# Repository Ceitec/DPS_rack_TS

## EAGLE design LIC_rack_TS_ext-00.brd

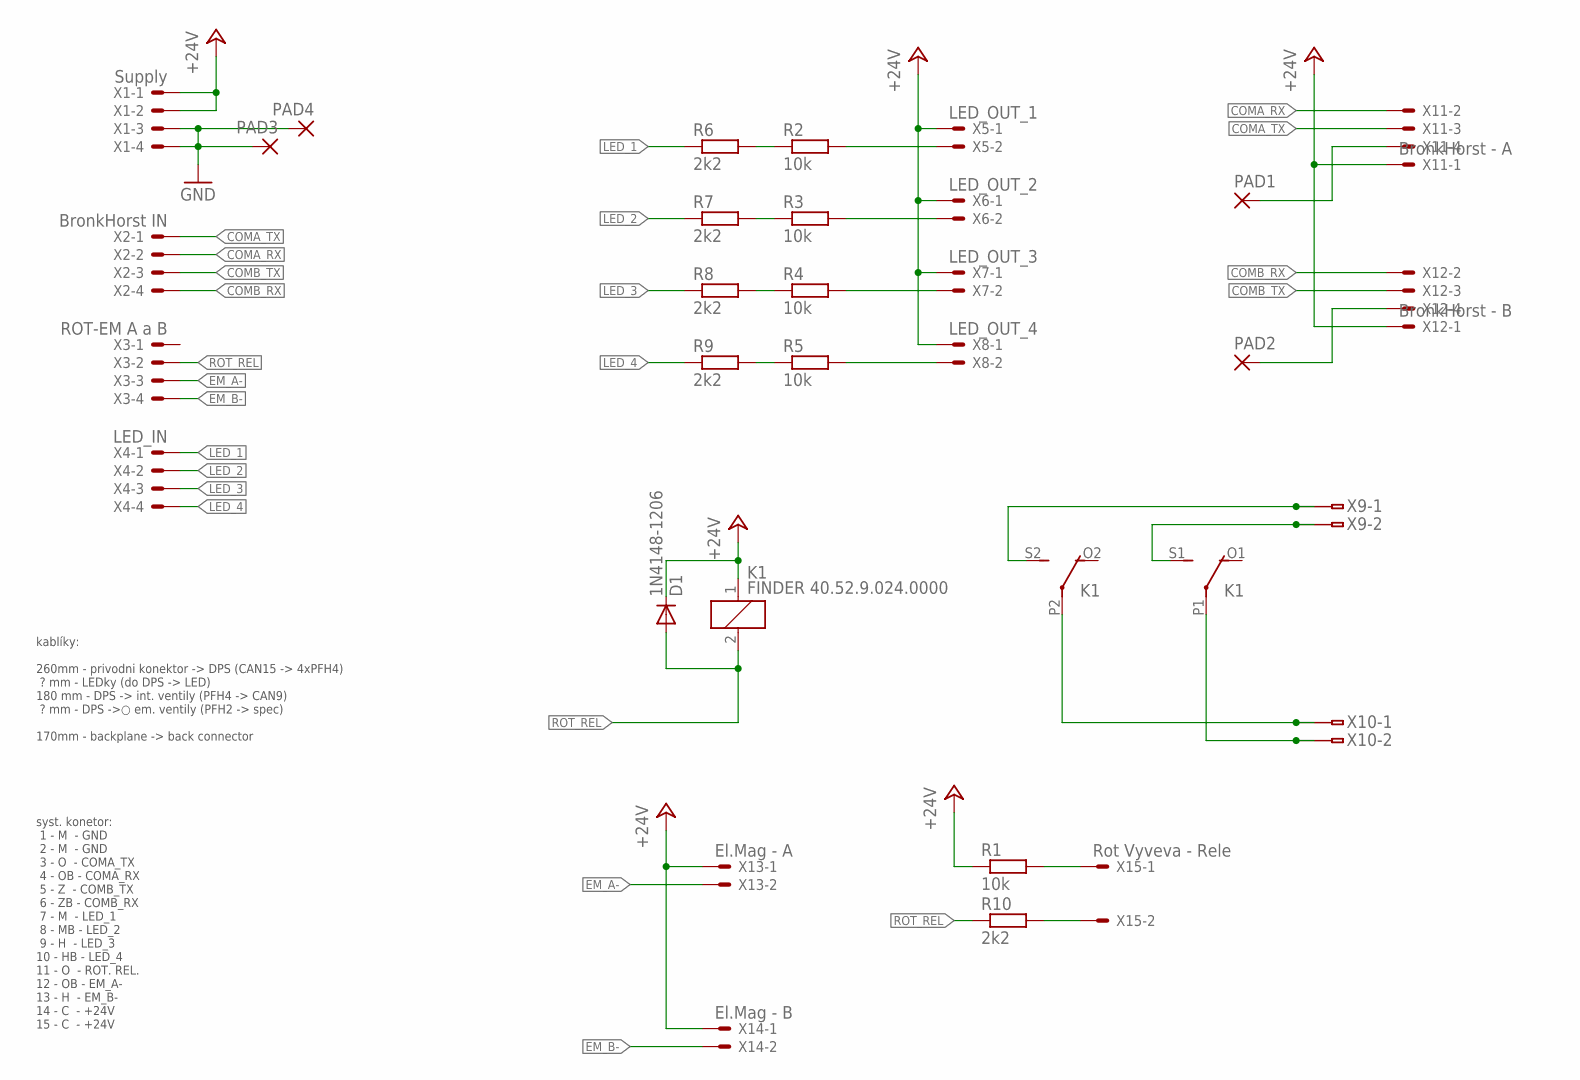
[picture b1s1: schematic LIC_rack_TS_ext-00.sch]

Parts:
D1: 1N4148-1206; R1206
K1: FINDER 40.52.9.024.0000; F4052
PAD1, PAD2, PAD3, PAD4: SMD-2X3; SMD2-3
R1, R2, R3, R4, R5: 10k; R1206
R6, R7, R8, R9, R10: 2k2; R1206
X1: Supply; 22-23-2041
X2: BronkHorst IN; 22-23-2041
X3: ROT-EM A a B; 22-23-2041
X4: LED_IN; 22-23-2041
X5: LED_OUT_1; 22-23-2021
X6: LED_OUT_2; 22-23-2021
X7: LED_OUT_3; 22-23-2021
X8: LED_OUT_4; 22-23-2021
X9: High Voltage Supply - L; WAGO236-401_2
X10: High Voltage Supply - N; WAGO236-401_2
X11: BronkHorst - A; 22-23-2041
X12: BronkHorst - B; 22-23-2041
X13: El.Mag - A; 22-23-2021
X14: El.Mag - B; 22-23-2021
X15: Rot Vyveva - Rele; 22-23-2021

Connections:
+24V: D1.K (C), K1.1, R1.1, X1.1, X1.2, X5.1, X6.1, X7.1, X8.1, X11.1, X12.1, X13.1, X14.1
COMA_RX: X2.2, X11.2
COMA_TX: X2.1, X11.3
COMB_RX: X2.4, X12.2
COMB_TX: X2.3, X12.3
EM_A-: X3.3, X13.2
EM_B-: X3.4, X14.2
GND: PAD3.1, PAD4.1, X1.3, X1.4
LED_1: R6.1, X4.1
LED_2: R7.1, X4.2
LED_3: R8.1, X4.3
LED_4: R9.1, X4.4
unnamed: K1.S1 (S), X9.2A (1), X9.2B (2)
unnamed: K1.S2 (S), X9.1A (1), X9.1B (2)
unnamed: K1.P1, X10.2A (1), X10.2B (2)
unnamed: K1.P2, X10.1A (1), X10.1B (2)
unnamed: R2.2, X5.2
unnamed: R3.2, X6.2
unnamed: R4.2, X7.2
unnamed: R5.2, X8.2
unnamed: R2.1, R6.2
unnamed: R3.1, R7.2
unnamed: R4.1, R8.2
unnamed: R5.1, R9.2
unnamed: PAD1.1, X11.4
unnamed: PAD2.1, X12.4
unnamed: R10.2, X15.2
unnamed: R1.2, X15.1
ROT_REL: D1.A, K1.2, R10.1, X3.2

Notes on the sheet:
kablíky: 260mm - privodni konektor -> DPS (CAN15 -> 4xPFH4) ? mm - LEDky (do DPS -> LED) 180 mm - DPS -> int. ventily (PFH4 -> CAN9) ? mm - DPS ->○ em. ventily (PFH2 -> spec) 170mm - backplane -> back connector
syst. konetor: 1 - M - GND 2 - M - GND 3 - O - COMA_TX 4 - OB - COMA_RX 5 - Z - COMB_TX 6 - ZB - COMB_RX 7 - M - LED_1 8 - MB - LED_2 9 - H - LED_3 10 - HB - LED_4 11 - O - ROT. REL. 12 - OB - EM_A- 13 - H - EM_B- 14 - C - +24V 15 - C - +24V

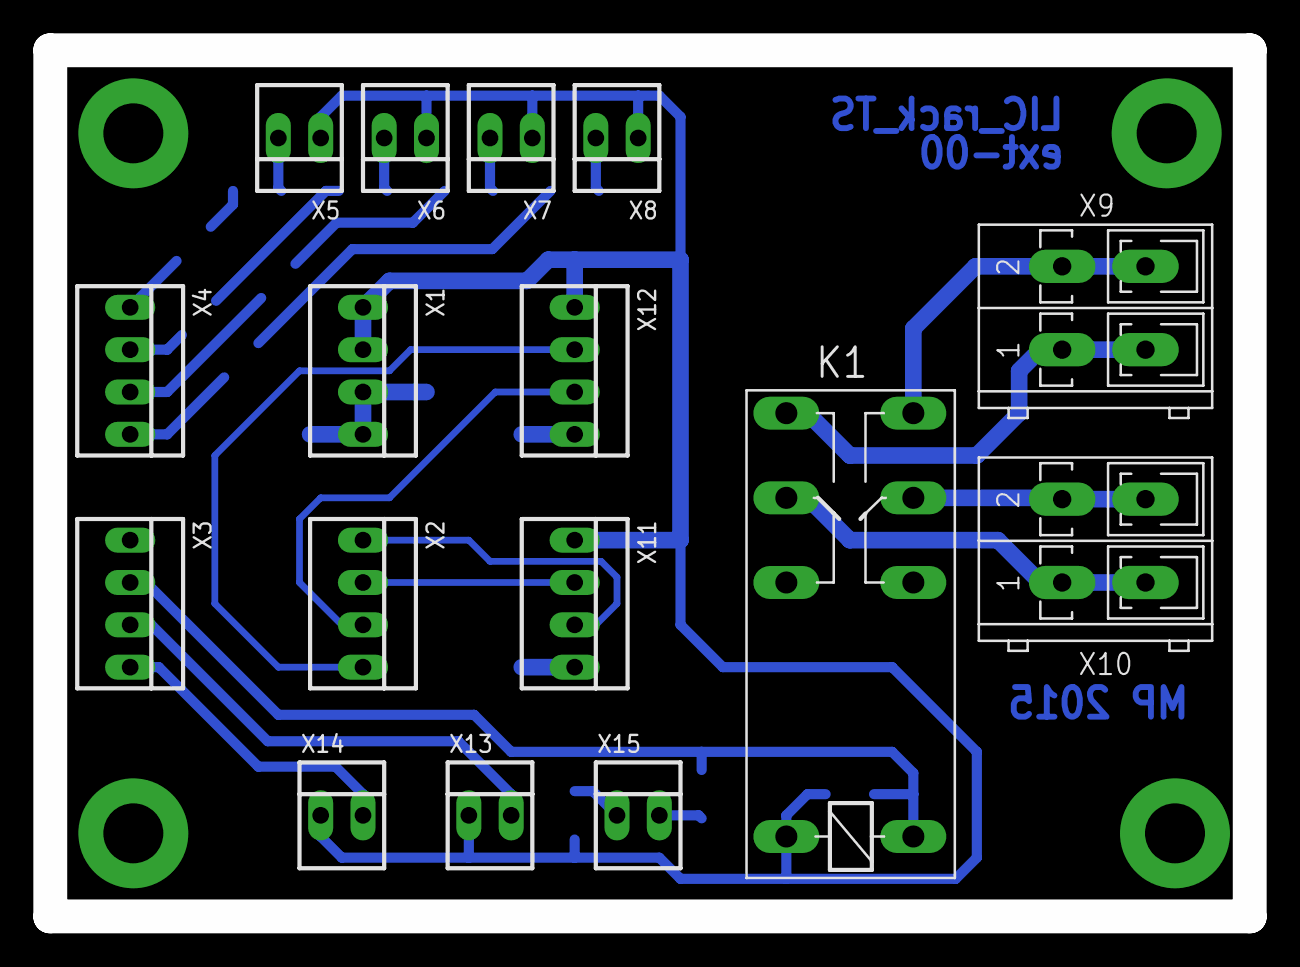
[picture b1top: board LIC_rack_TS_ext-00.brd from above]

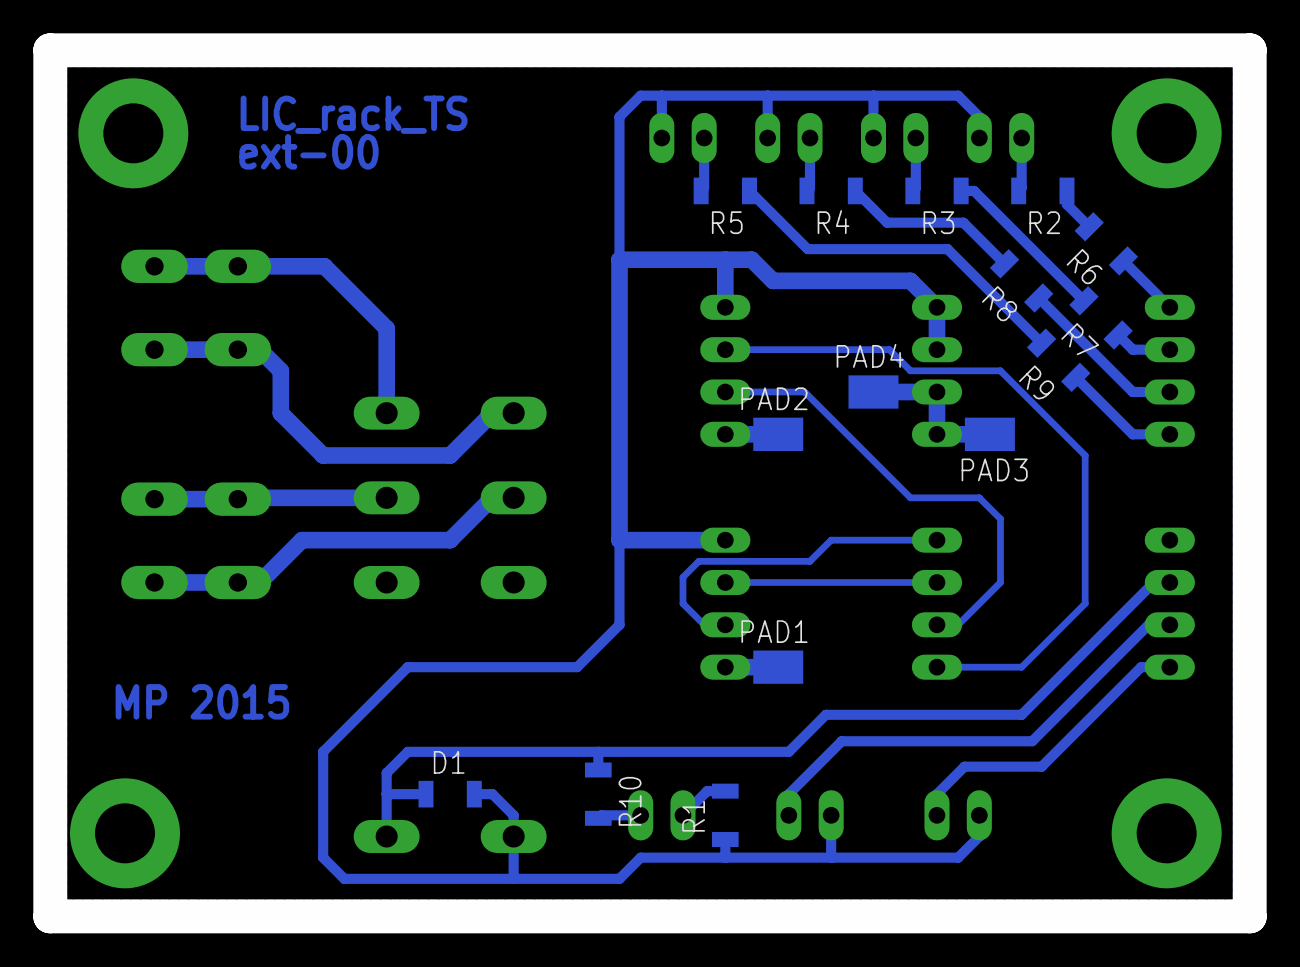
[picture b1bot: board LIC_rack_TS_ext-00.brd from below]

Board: 2 copper layers, 72.0 x 52.0 mm, 32 parts (15 on the bottom side), 29 nets.

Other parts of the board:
U$2: A4L-LOC

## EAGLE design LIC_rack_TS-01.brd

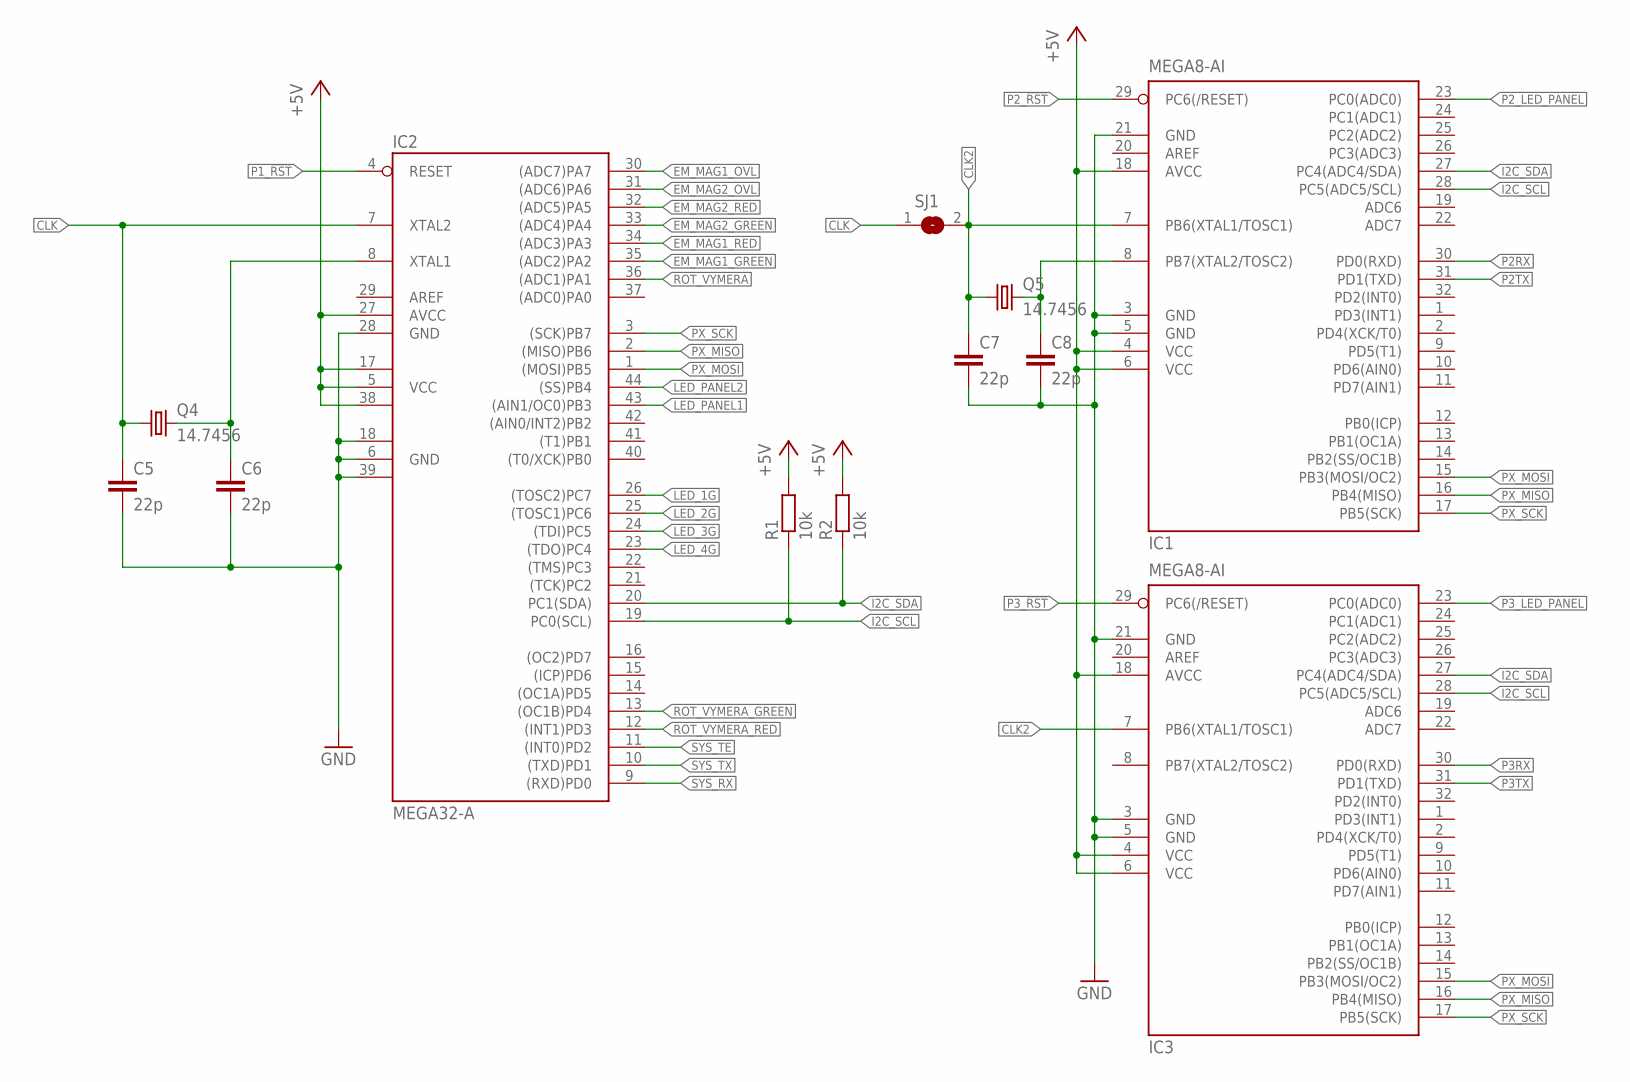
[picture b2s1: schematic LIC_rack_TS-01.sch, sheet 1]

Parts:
C5, C6, C7, C8: 22p; C0805
IC1, IC3: MEGA8-AI; TQFP32-08
IC2: MEGA32-A; TQFP44
Q4, Q5: 14.7456; HC49U70
R1, R2: 10k; R1206
SJ1: SJ-DEFAULT; SJ-D

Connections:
+5V: IC1.4 (VCC), IC1.6 (VCC), IC1.18 (AVCC), IC2.5 (VCC), IC2.17 (VCC1), IC2.27 (AVCC), IC2.38 (VCC2), IC3.4 (VCC), IC3.6 (VCC), IC3.18 (AVCC), R1.2, R2.2; also elsewhere on the board
CLK: C5.1, IC2.7 (XTAL2), Q4.1, SJ1.1
CLK2: C7.1, IC1.7 (PB6(XTAL1/TOSC1)), IC3.7 (PB6(XTAL1/TOSC1)), Q5.1, SJ1.2
EM_MAG1_GREEN: IC2.35 ((ADC2)PA2); also elsewhere on the board
EM_MAG1_OVL: IC2.30 ((ADC7)PA7); also elsewhere on the board
EM_MAG1_RED: IC2.34 ((ADC3)PA3); also elsewhere on the board
EM_MAG2_GREEN: IC2.33 ((ADC4)PA4); also elsewhere on the board
EM_MAG2_OVL: IC2.31 ((ADC6)PA6); also elsewhere on the board
EM_MAG2_RED: IC2.32 ((ADC5)PA5); also elsewhere on the board
GND: C5.2, C6.2, C7.2, C8.2, IC1.3 (GND), IC1.5 (GND), IC1.21 (GND), IC2.6 (GND), IC2.18 (GND1), IC2.28 (GND), IC2.39 (GND2), IC3.3 (GND), IC3.5 (GND), IC3.21 (GND); also elsewhere on the board
I2C_SCL: IC1.28 (PC5(ADC5/SCL)), IC2.19 (PC0(SCL)), IC3.28 (PC5(ADC5/SCL)), R1.1; also elsewhere on the board
I2C_SDA: IC1.27 (PC4(ADC4/SDA)), IC2.20 (PC1(SDA)), IC3.27 (PC4(ADC4/SDA)), R2.1; also elsewhere on the board
LED_1G: IC2.26 ((TOSC2)PC7); also elsewhere on the board
LED_2G: IC2.25 ((TOSC1)PC6); also elsewhere on the board
LED_3G: IC2.24 ((TDI)PC5); also elsewhere on the board
LED_4G: IC2.23 ((TDO)PC4); also elsewhere on the board
LED_PANEL1: IC2.43 ((AIN1/OC0)PB3); also elsewhere on the board
LED_PANEL2: IC2.44 ((SS)PB4); also elsewhere on the board
unnamed: C8.1, IC1.8 (PB7(XTAL2/TOSC2)), Q5.2
unnamed: C6.1, IC2.8 (XTAL1), Q4.2
P1_!RST: IC2.4 (RESET); also elsewhere on the board
P2RX: IC1.30 (PD0(RXD)); also elsewhere on the board
P2TX: IC1.31 (PD1(TXD)); also elsewhere on the board
P2_!RST: IC1.29 (PC6(/RESET)); also elsewhere on the board
P2_LED_PANEL: IC1.23 (PC0(ADC0)); also elsewhere on the board
P3RX: IC3.30 (PD0(RXD)); also elsewhere on the board
P3TX: IC3.31 (PD1(TXD)); also elsewhere on the board
P3_!RST: IC3.29 (PC6(/RESET)); also elsewhere on the board
P3_LED_PANEL: IC3.23 (PC0(ADC0)); also elsewhere on the board
PX_MISO: IC1.16 (PB4(MISO)), IC2.2 ((MISO)PB6), IC3.16 (PB4(MISO)); also elsewhere on the board
PX_MOSI: IC1.15 (PB3(MOSI/OC2)), IC2.1 ((MOSI)PB5), IC3.15 (PB3(MOSI/OC2)); also elsewhere on the board
PX_SCK: IC1.17 (PB5(SCK)), IC2.3 ((SCK)PB7), IC3.17 (PB5(SCK)); also elsewhere on the board
ROT_VYMERA: IC2.36 ((ADC1)PA1); also elsewhere on the board
ROT_VYMERA_GREEN: IC2.13 ((OC1B)PD4); also elsewhere on the board
ROT_VYMERA_RED: IC2.12 ((INT1)PD3); also elsewhere on the board
SYS_RX: IC2.9 ((RXD)PD0); also elsewhere on the board
SYS_TE: IC2.11 ((INT0)PD2); also elsewhere on the board
SYS_TX: IC2.10 ((TXD)PD1); also elsewhere on the board

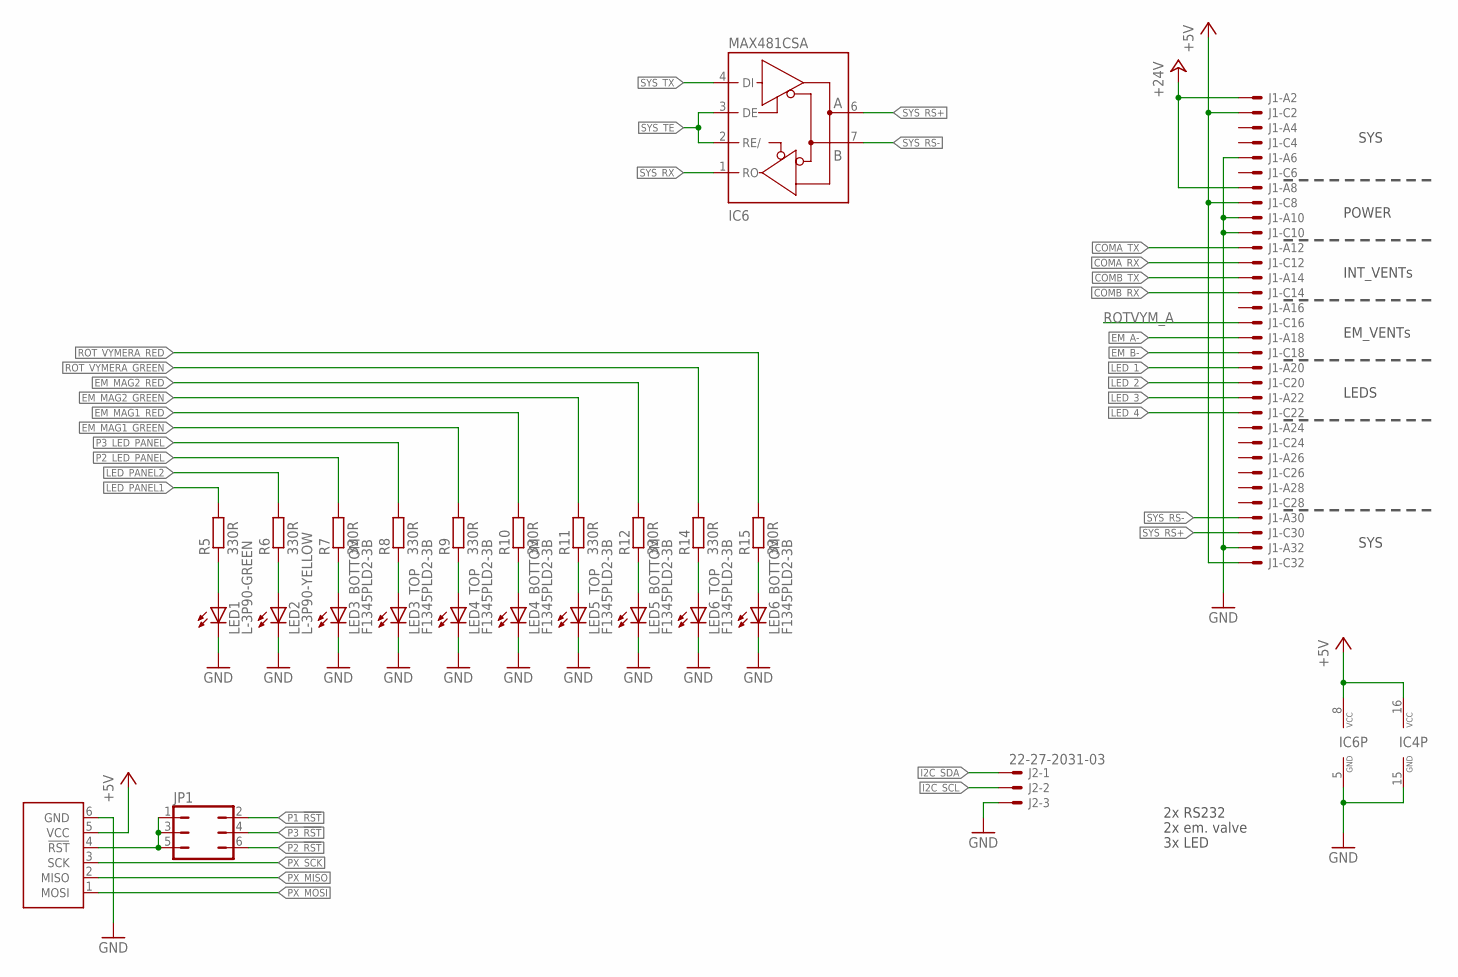
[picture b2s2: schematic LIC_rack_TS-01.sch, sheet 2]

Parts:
IC4: MAX232; DIL16
IC6: MAX481CSA; SO08
J1: VG32SP; VG32P
J2: 22-27-2031-03; 6410-03
JP1: JP3Q
LED1: L-3P90-GREEN; L-3P90
LED2: L-3P90-YELLOW; L-3P90
LED3, LED4, LED5, LED6: F1345PLD2-3B
R5, R6, R7, R8, R9, R10, R11, R12, R14, R15: 330R; R1206
U1: ATPROG-V; 6410-06

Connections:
+5V: IC4.16 (VCC), IC6.8 (VCC), J1.C2 (MS), J1.C8 (MS), J1.C32 (MSV), U1.5 (VCC); also elsewhere on the board
+24V: J1.A2 (MS), J1.A8 (MS)
COMA_RX: J1.C12 (MS); also elsewhere on the board
COMA_TX: J1.A12 (MS); also elsewhere on the board
COMB_RX: J1.C14 (MS); also elsewhere on the board
COMB_TX: J1.A14 (MS); also elsewhere on the board
EM_A-: J1.A18 (MS); also elsewhere on the board
EM_B-: J1.C18 (MS); also elsewhere on the board
EM_MAG1_GREEN: R9.2; also elsewhere on the board
EM_MAG1_RED: R10.2; also elsewhere on the board
EM_MAG2_GREEN: R11.2; also elsewhere on the board
EM_MAG2_RED: R12.2; also elsewhere on the board
GND: IC4.15 (GND), IC6.5 (GND), J1.A6 (MS), J1.A10 (MS), J1.A32 (MS), J1.C10 (MS), J2.3, LED1.K (C), LED2.K (C), LED3.1K (C), LED3.2K (C), LED4.1K (C), LED4.2K (C), LED5.1K (C), LED5.2K (C), LED6.1K (C), LED6.2K (C), U1.6 (GND); also elsewhere on the board
I2C_SCL: J2.2; also elsewhere on the board
I2C_SDA: J2.1; also elsewhere on the board
LED_1: J1.A20 (MS); also elsewhere on the board
LED_2: J1.C20 (MS); also elsewhere on the board
LED_3: J1.A22 (MS); also elsewhere on the board
LED_4: J1.C22 (MS); also elsewhere on the board
LED_PANEL1: R5.2; also elsewhere on the board
LED_PANEL2: R6.2; also elsewhere on the board
unnamed: LED2.A, R6.1
unnamed: LED1.A, R5.1
unnamed: LED4.1A (A), R10.1
unnamed: LED4.2A (A), R9.1
unnamed: LED3.2A (A), R8.1
unnamed: LED3.1A (A), R7.1
unnamed: LED5.2A (A), R11.1
unnamed: LED5.1A (A), R12.1
unnamed: LED6.2A (A), R14.1
unnamed: LED6.1A (A), R15.1
P1_!RST: JP1.2; also elsewhere on the board
P2_!RST: JP1.6; also elsewhere on the board
P2_LED_PANEL: R7.2; also elsewhere on the board
P3_!RST: JP1.4; also elsewhere on the board
P3_LED_PANEL: R8.2; also elsewhere on the board
PROG_!RST: JP1.1, JP1.3, JP1.5, U1.4 (!RST)
PX_MISO: U1.2 (MISO); also elsewhere on the board
PX_MOSI: U1.1 (MOSI); also elsewhere on the board
PX_SCK: U1.3 (SCK); also elsewhere on the board
ROTVYM_A: J1.C16 (MS); also elsewhere on the board
ROT_VYMERA_GREEN: R14.2; also elsewhere on the board
ROT_VYMERA_RED: R15.2; also elsewhere on the board
SYS_RS+: IC6.6 (A), J1.C30 (MS)
SYS_RS-: IC6.7 (B), J1.A30 (MS)
SYS_RX: IC6.1 (RO); also elsewhere on the board
SYS_TE: IC6.2 (RE/), IC6.3 (DE); also elsewhere on the board
SYS_TX: IC6.4 (DI); also elsewhere on the board

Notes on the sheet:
2x RS232
2x em. valve
3x LED
SYS
POWER
INT_VENTs
EM_VENTs
LEDS

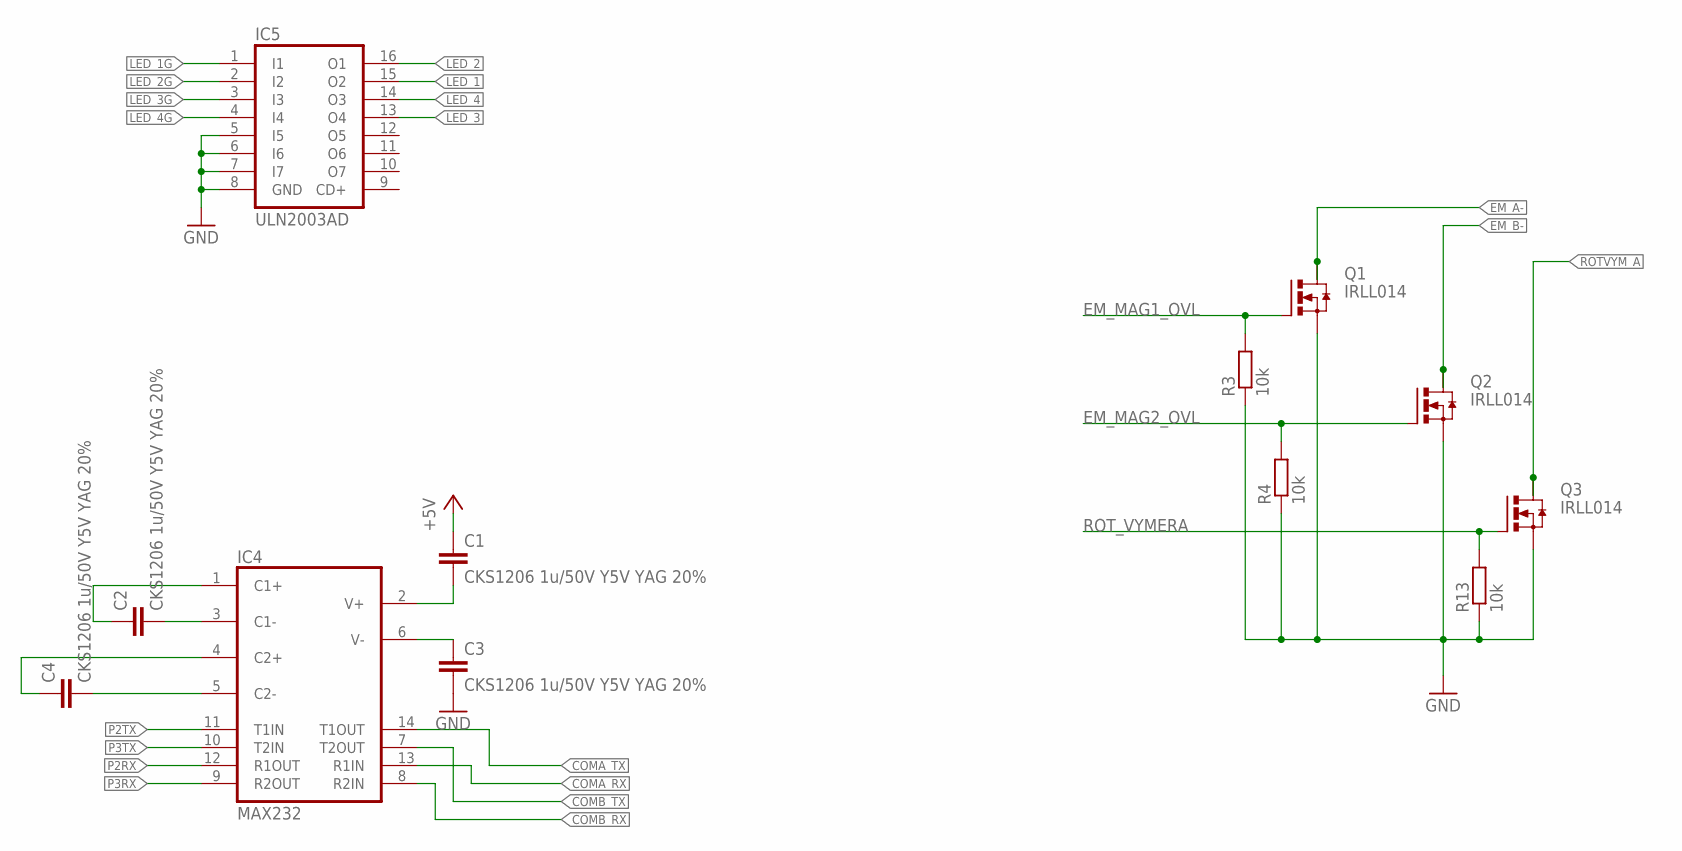
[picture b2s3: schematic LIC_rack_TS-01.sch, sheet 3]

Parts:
C1, C2, C3, C4: CKS1206 1u/50V Y5V YAG 20%; C1206
IC4: MAX232; DIL16
IC5: ULN2003AD; SO16
Q1, Q2, Q3: IRLL014; SOT223
R3, R4, R13: 10k; R1206

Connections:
+5V: C1.1; also elsewhere on the board
COMA_RX: IC4.13 (R1IN); also elsewhere on the board
COMA_TX: IC4.14 (T1OUT); also elsewhere on the board
COMB_RX: IC4.8 (R2IN); also elsewhere on the board
COMB_TX: IC4.7 (T2OUT); also elsewhere on the board
EM_A-: Q1.2 (D), Q1.4 (D); also elsewhere on the board
EM_B-: Q2.2 (D), Q2.4 (D); also elsewhere on the board
EM_MAG1_OVL: Q1.1 (G), R3.2; also elsewhere on the board
EM_MAG2_OVL: Q2.1 (G), R4.2; also elsewhere on the board
GND: C3.2, IC5.5 (I5), IC5.6 (I6), IC5.7 (I7), IC5.8 (GND), Q1.3 (S), Q2.3 (S), Q3.3 (S), R3.1, R4.1, R13.1; also elsewhere on the board
LED_1: IC5.15 (O2); also elsewhere on the board
LED_1G: IC5.1 (I1); also elsewhere on the board
LED_2: IC5.16 (O1); also elsewhere on the board
LED_2G: IC5.2 (I2); also elsewhere on the board
LED_3: IC5.13 (O4); also elsewhere on the board
LED_3G: IC5.3 (I3); also elsewhere on the board
LED_4: IC5.14 (O3); also elsewhere on the board
LED_4G: IC5.4 (I4); also elsewhere on the board
unnamed: C4.2, IC4.5 (C2-)
unnamed: C4.1, IC4.4 (C2+)
unnamed: C2.2, IC4.3 (C1-)
unnamed: C2.1, IC4.1 (C1+)
unnamed: C1.2, IC4.2 (V+)
unnamed: C3.1, IC4.6 (V-)
P2RX: IC4.12 (R1OUT); also elsewhere on the board
P2TX: IC4.11 (T1IN); also elsewhere on the board
P3RX: IC4.9 (R2OUT); also elsewhere on the board
P3TX: IC4.10 (T2IN); also elsewhere on the board
ROTVYM_A: Q3.2 (D), Q3.4 (D); also elsewhere on the board
ROT_VYMERA: Q3.1 (G), R13.2; also elsewhere on the board

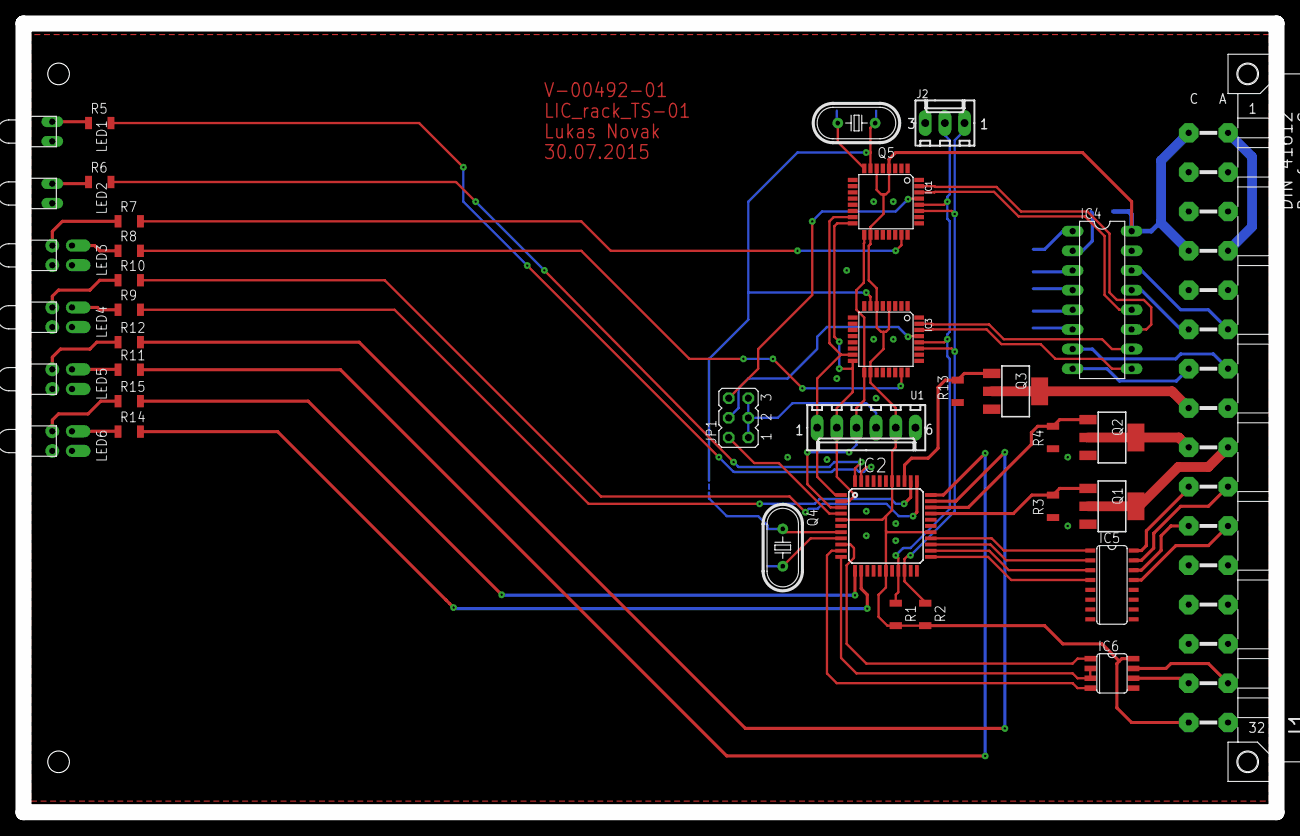
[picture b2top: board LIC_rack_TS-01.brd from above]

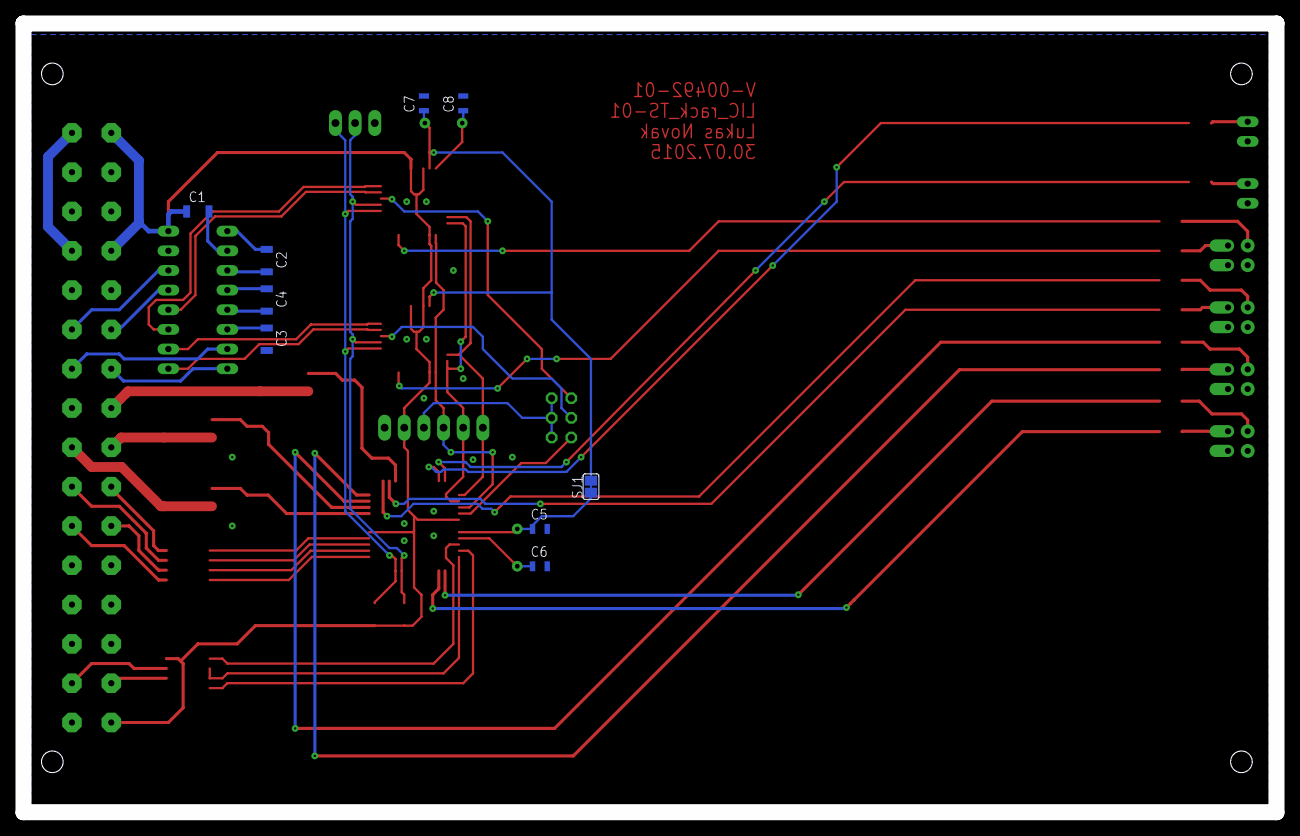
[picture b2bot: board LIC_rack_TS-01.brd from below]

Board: 2 copper layers, 162.0 x 102.0 mm, 45 parts (9 on the bottom side), 69 nets.

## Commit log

2015-08-11 :lollipop: Added .gitattributes & .gitignore files
2015-08-11 Tlakový systém
2016-02-10 v.1.0
